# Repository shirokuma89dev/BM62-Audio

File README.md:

# BM62-Audio
BM62を使っていい感じのオーディオを作ろう！！！！！！！

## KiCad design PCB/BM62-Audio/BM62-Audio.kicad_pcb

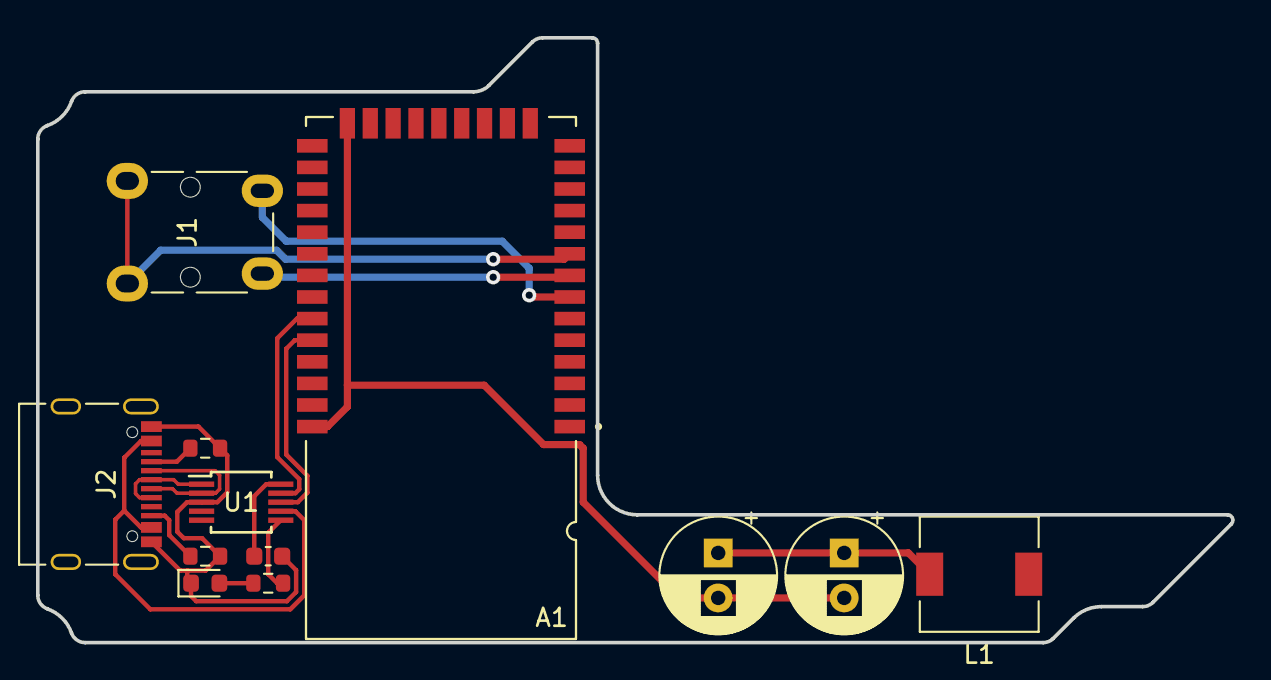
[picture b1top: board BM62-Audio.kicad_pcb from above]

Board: 2 copper layers, 66.4 x 33.6 mm, 12 parts (0 on the bottom side), 15 nets.

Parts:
A1: BM62SPKA1MC2-0001AA; MICROCHIP_BM62SPKA1MC2-0001AA
C1: 0.1µ; C_0603_1608Metric
C2, C3: 100µ; CP_Radial_D6.3mm_P2.50mm
D1: WHITE; LED_0603_1608Metric
J1: AudioJack3; Jack_3.5mm_Lumberg_1503_07_Horizontal
J2: USB_C_Receptacle_USB2.0; USB_C_Receptacle_Palconn_UTC16-G
L1: 47µ; L_6.3x6.3_H3
R1, R2: 5.1k; R_0603_1608Metric
R3: 1k; R_0603_1608Metric
U1: CH340E; MSOP-10_3x3mm_P0.5mm

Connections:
+5V: J2.A4 (VBUS), J2.A9 (VBUS), J2.B4 (VBUS), J2.B9 (VBUS), U1.7 (VCC)
/AUDIO OUT COM: A1.8 (AOHPM), J1.S
/AUDIO OUT Lch: A1.9 (SPKL), J1.T
/AUDIO OUT Rch: A1.7 (SPKR), J1.R
/D+: J2.A6 (D+), J2.B6 (D+), U1.1 (UD+)
/D-: J2.A7 (D-), J2.B7 (D-), U1.2 (UD-)
/USB-RX BM62-TX: A1.32 (HCI_TXD), U1.9 (RXD)
/USB-TX BM62-RX: A1.33 (HCI_RXD), U1.8 (TXD)
GND: A1.23 (GND), A1.37 (GND__1), C1.2, C2.2, C3.2, D1.1 (K), J2.A1 (GND), J2.A12 (GND), J2.B1 (GND), J2.B12 (GND), R1.2, R2.2, U1.3 (GND)
unnamed: C2.1, C3.1, L1.2
unnamed: D1.2 (A), R3.1
unnamed: J2.A5 (CC1), R1.1
unnamed: J2.B5 (CC2), R2.1
unnamed: R3.2, U1.6 (TNOW)
unnamed: C1.1, U1.10 (V3)

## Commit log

2023-11-27 ✨ ライセンスをCC BY-NC-SA 4.0に変更
2023-11-27 ✏️gitignore
2023-11-27 ✨ 外形寸法
2023-11-27 ✨ 基板のプロジェクト作成
2023-11-27 🐛 .DS_Storeを消しました
2023-11-28 ✨ KiCADファイル作りました
2023-12-02 ✏️ 回路図の基礎ができた
